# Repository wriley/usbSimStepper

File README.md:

usbSimStepper
=============

This is a half-finished project I started several years ago for a flight simulator panel. It is a USB driver board for 1-2 stepper motors built for instruments from Mike Powell's book Building Simulated Aircraft Instrumentation<sup>1</sup>. Windows programs, such as usbSimCentral<sup>2</sup>, can interface with this board via a DLL<sup>3</sup>.

Relevant blog posts
* http://workbench.freetcp.com/archives/549
* http://workbench.freetcp.com/archives/555
* http://workbench.freetcp.com/archives/571
* http://workbench.freetcp.com/archives/739
* http://workbench.freetcp.com/archives/745

References

1. http://www.mikesflightdeck.com/mfdb/bsai/bsai.html
2. https://github.com/wriley/usbSimCentral
3. https://github.com/wriley/usbSimInstrument

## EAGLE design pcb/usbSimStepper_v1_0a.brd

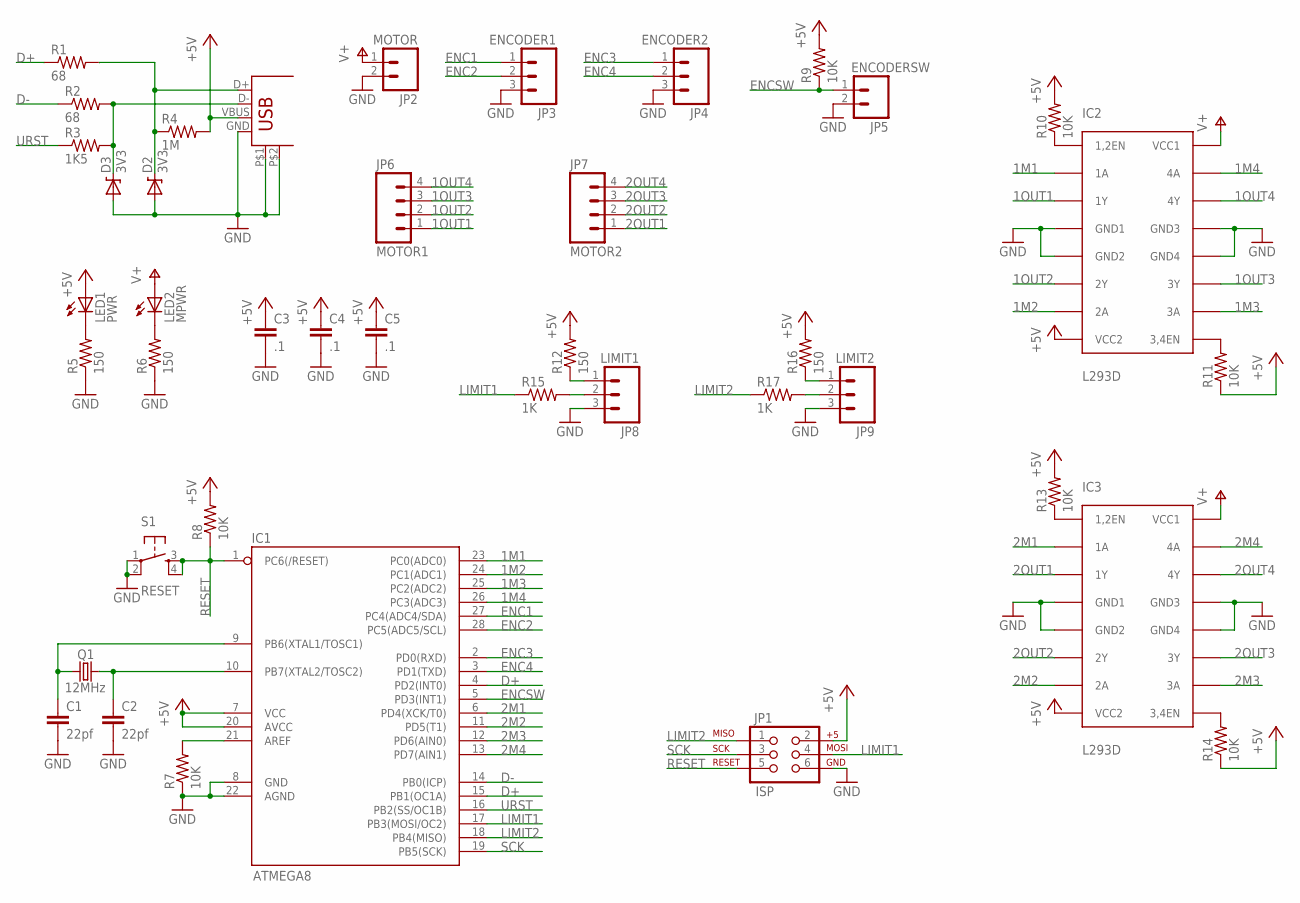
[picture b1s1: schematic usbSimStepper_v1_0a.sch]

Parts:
C1, C2: 22pf; CAP-PTH-SMALL2
C3, C4, C5: .1; CAP-PTH-SMALL2
D2, D3: 3V3; DIODE-ZENER
IC1: ATMEGA8; DIL28-3
IC2, IC3: L293D; DIL16
JP1: ISP; 2X3-NS
JP2: MOTOR; MOLEX-1X2
JP3: ENCODER1; MOLEX-1X3
JP4: ENCODER2; MOLEX-1X3
JP5: ENCODERSW; MOLEX-1X2
JP6: MOTOR1; MOLEX-1X4
JP7: MOTOR2; MOLEX-1X4
JP8: LIMIT1; MOLEX-1X3
JP9: LIMIT2; MOLEX-1X3
LED1: PWR; LED5MM
LED2: MPWR; LED5MM
Q1: 12MHz; HC49US
R1, R2: 68; 0204/7
R3: 1K5; 0204/7
R4: 1M; 0204/7
R5, R6, R12, R16: 150; 0204/7
R7, R8, R9, R10, R11, R13, R14: 10K; 0204/7
R15, R17: 1K; 0204/7
S1: RESET; TACTILE-PTH
X1: USB; USB-B-PTH-VERTICAL

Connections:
1M1: IC1.23 (PC0(ADC0)), IC2.2 (1A)
1M2: IC1.24 (PC1(ADC1)), IC2.7 (2A)
1M3: IC1.25 (PC2(ADC2)), IC2.10 (3A)
1M4: IC1.26 (PC3(ADC3)), IC2.15 (4A)
1OUT1: IC2.3 (1Y), JP6.1
1OUT2: IC2.6 (2Y), JP6.2
1OUT3: IC2.11 (3Y), JP6.3
1OUT4: IC2.14 (4Y), JP6.4
2M1: IC1.6 (PD4(XCK/T0)), IC3.2 (1A)
2M2: IC1.11 (PD5(T1)), IC3.7 (2A)
2M3: IC1.12 (PD6(AIN0)), IC3.10 (3A)
2M4: IC1.13 (PD7(AIN1)), IC3.15 (4A)
2OUT1: IC3.3 (1Y), JP7.1
2OUT2: IC3.6 (2Y), JP7.2
2OUT3: IC3.11 (3Y), JP7.3
2OUT4: IC3.14 (4Y), JP7.4
+5V: C3.1, C4.1, C5.1, IC1.7 (VCC), IC1.20 (AVCC), IC2.8 (VCC2), IC3.8 (VCC2), JP1.2, LED1.A, R4.2, R8.2, R9.2, R10.2, R11.1, R12.2, R13.2, R14.1, R16.2, X1.VBUS
D+: IC1.4 (PD2(INT0)), IC1.15 (PB1(OC1A)), R1.1
D-: IC1.14 (PB0(ICP)), R2.1
ENC1: IC1.27 (PC4(ADC4/SDA)), JP3.1
ENC2: IC1.28 (PC5(ADC5/SCL)), JP3.2
ENC3: IC1.2 (PD0(RXD)), JP4.1
ENC4: IC1.3 (PD1(TXD)), JP4.2
ENCSW: IC1.5 (PD3(INT1)), JP5.1, R9.1
GND: C1.2, C2.2, C3.2, C4.2, C5.2, D2.P$2 (A), D3.P$2 (A), IC1.8 (GND), IC1.22 (AGND), IC2.4 (GND1), IC2.5 (GND2), IC2.12 (GND4), IC2.13 (GND3), IC3.4 (GND1), IC3.5 (GND2), IC3.12 (GND4), IC3.13 (GND3), JP1.6, JP2.2, JP3.3, JP4.3, JP5.2, JP8.3, JP9.3, R5.1, R6.1, R7.1, S1.1, S1.2, X1.GND, X1.P$1, X1.P$2
LIMIT1: IC1.17 (PB3(MOSI/OC2)), JP1.4, R15.1
LIMIT2: IC1.18 (PB4(MISO)), JP1.1, R17.1
unnamed: D3.P$1 (C), R2.2, R3.2, X1.D-
unnamed: D2.P$1 (C), R1.2, R4.1, X1.D+
unnamed: LED1.K (C), R5.2
unnamed: LED2.K (C), R6.2
unnamed: C1.1, IC1.9 (PB6(XTAL1/TOSC1)), Q1.1
unnamed: C2.1, IC1.10 (PB7(XTAL2/TOSC2)), Q1.2
unnamed: IC1.21 (AREF), R7.2
unnamed: JP8.1, R12.1
unnamed: JP8.2, R15.2
unnamed: JP9.1, R16.1
unnamed: IC3.1 (1,2EN), R13.1
unnamed: IC3.9 (3,4EN), R14.2
unnamed: IC2.1 (1,2EN), R10.1
unnamed: IC2.9 (3,4EN), R11.2
unnamed: JP9.2, R17.2
RESET: IC1.1 (PC6(/RESET)), JP1.5, R8.1, S1.3, S1.4
SCK: IC1.19 (PB5(SCK)), JP1.3
URST: IC1.16 (PB2(SS/OC1B)), R3.1
V+: IC2.16 (VCC1), IC3.16 (VCC1), JP2.1, LED2.A

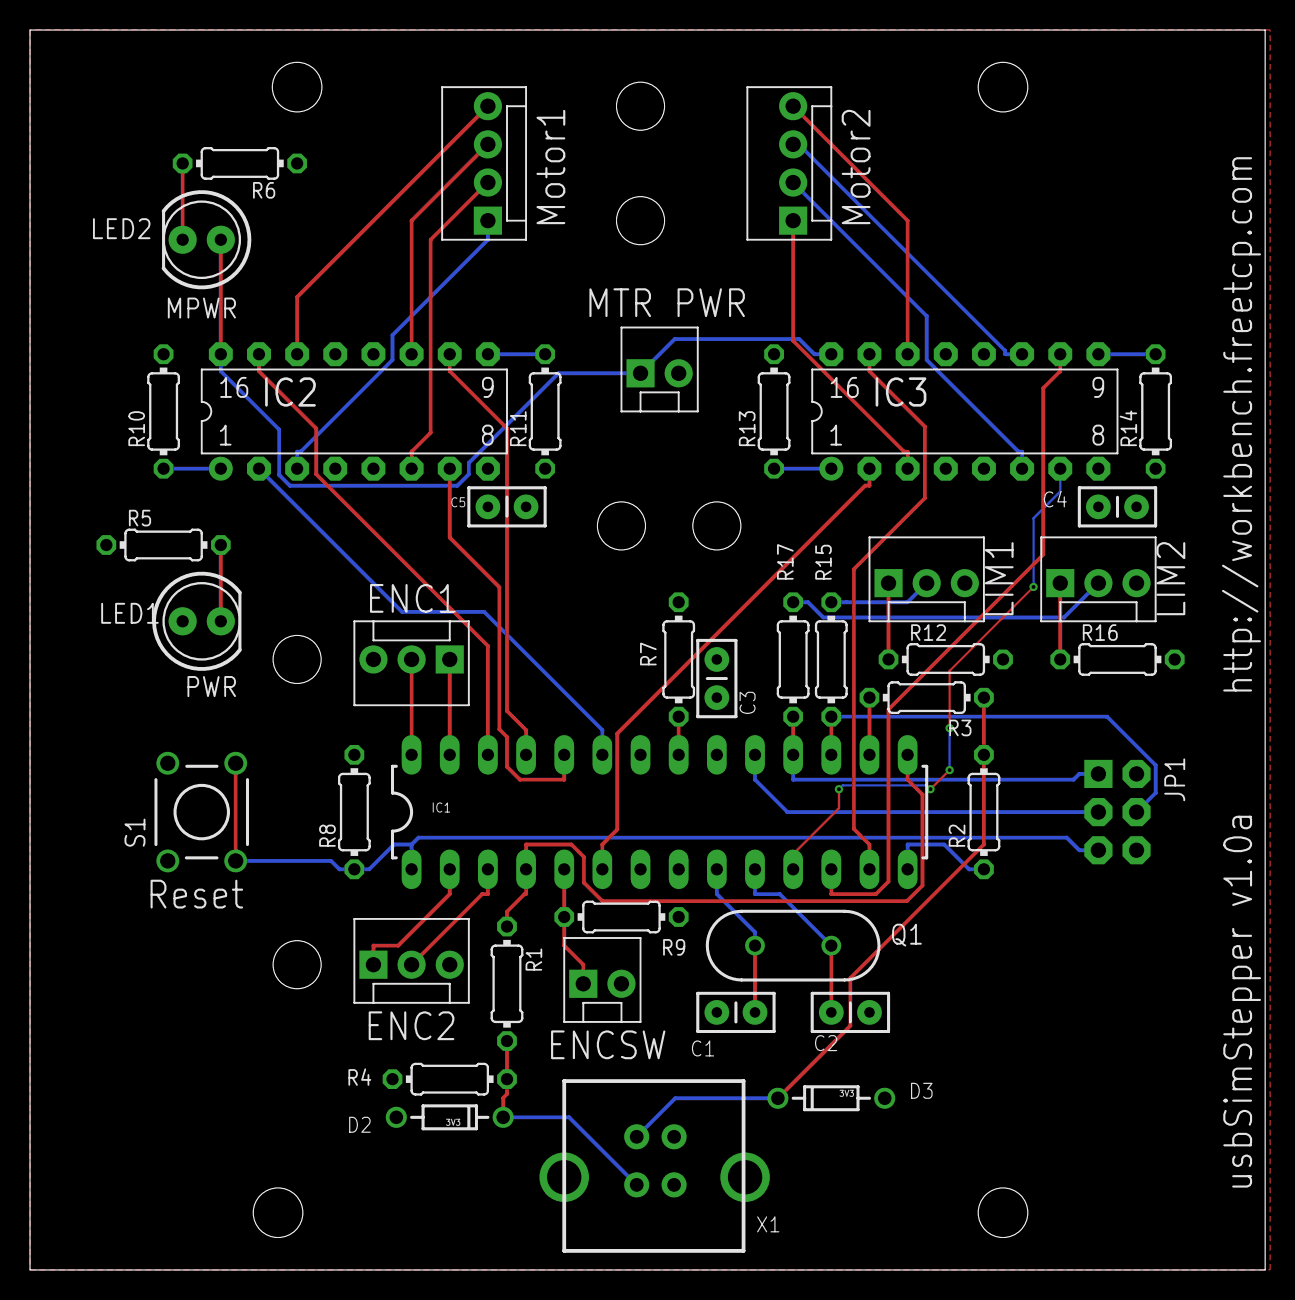
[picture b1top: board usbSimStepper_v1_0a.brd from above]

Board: 2 copper layers, 82.2 x 82.5 mm, 45 parts (0 on the bottom side), 46 nets.

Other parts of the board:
U$1, U$2, U$3, U$4: STAND-OFF

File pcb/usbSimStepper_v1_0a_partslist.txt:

Partlist

Exported from usbSimStepper_v1_0a.brd at 2/13/2012 9:21:40 PM

EAGLE Version 6.1.0 Copyright (c) 1988-2012 CadSoft

Assembly variant: 

Part     Value          Package            Library  Position (inch)       Orientation

C1       22pf           CAP-PTH-SMALL2     SparkFun (1.9 0.675)           R180
C2       22pf           CAP-PTH-SMALL2     SparkFun (2.1 0.675)           R0
C3       .1             CAP-PTH-SMALL2     SparkFun (1.8 1.5)             R90
C4       .1             CAP-PTH-SMALL2     SparkFun (2.8 2)               R0
C5       .1             CAP-PTH-SMALL2     SparkFun (1.2 2)               R0
D2       3V3            DIODE-ZENER        SparkFun (1.1 0.4)             R180
D3       3V3            DIODE-ZENER        SparkFun (2.1 0.45)            R0
IC1      ATMEGA8        DIL28-3            SparkFun (1.65 1.2)            R0
IC2      L293D          DIL16              sgs-thom (0.85 2.25)           R0
IC3      L293D          DIL16              sgs-thom (2.45 2.25)           R0
JP1      ISP            2X3-NS             SparkFun (2.85 1.2)            R270
JP2      MOTOR          MOLEX-1X2          SparkFun (1.6 2.35)            R0
JP3      ENCODER1       MOLEX-1X3          SparkFun (1.1 1.6)             R180
JP4      ENCODER2       MOLEX-1X3          SparkFun (0.9 0.8)             R0
JP5      ENCODERSW      MOLEX-1X2          SparkFun (1.45 0.75)           R0
JP6      MOTOR1         MOLEX-1X4          SparkFun (1.2 2.75)            R90
JP7      MOTOR2         MOLEX-1X4          SparkFun (2 2.75)              R90
JP8      LIMIT1         MOLEX-1X3          SparkFun (2.25 1.8)            R0
JP9      LIMIT2         MOLEX-1X3          SparkFun (2.7 1.8)             R0
LED1     PWR            LED5MM             SparkFun (0.45 1.7)            R0
LED2     MPWR           LED5MM             SparkFun (0.45 2.7)            R180
Q1       12MHz          HC49US             SparkFun (2 0.85)              R0
R1       68             0204/7             resistor (1.25 0.75)           R270
R2       68             0204/7             resistor (2.5 1.2)             R90
R3       1K5            0204/7             resistor (2.35 1.5)            R0
R4       1M             0204/7             resistor (1.1 0.5)             R180
R5       150            0204/7             resistor (0.35 1.9)            R0
R6       150            0204/7             resistor (0.55 2.9)            R180
R7       10K            0204/7             resistor (1.7 1.6)             R270
R8       10K            0204/7             resistor (0.85 1.2)            R90
R9       10K            0204/7             resistor (1.55 0.925)          R0
R10      10K            0204/7             resistor (0.35 2.25)           R90
R11      10K            0204/7             resistor (1.35 2.25)           R90
R12      150            0204/7             resistor (2.4 1.6)             R0
R13      10K            0204/7             resistor (1.95 2.25)           R90
R14      10K            0204/7             resistor (2.95 2.25)           R90
R15      1K             0204/7             resistor (2.1 1.6)             R90
R16      150            0204/7             resistor (2.85 1.6)            R0
R17      1K             0204/7             resistor (2 1.6)               R90
S1       RESET          TACTILE-PTH        SparkFun (0.45 1.2)            R90
X1       USB            USB-B-PTH-VERTICAL SparkFun (1.4 0.05)            R0

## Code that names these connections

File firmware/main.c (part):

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
    wdt_enable(WDTO_1S);
    odDebugInit();
    DDRD = ~(1 << 2);   /* all outputs except PD2 = INT0 */
    PORTD = 0;
    PORTB = 0;          /* no pullups on USB pins */
/* We fake an USB disconnect by pulling D+ and D- to 0 during reset. This is
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    TCCR0 = 5;          /* set prescaler to 1/1024 */
    usbInit();

	DDRB &= ~(_BV(PB3));
	PORTB |= _BV(PB3);
	
	DDRD &= ~(_BV(PD0)|_BV(PD1));
	PORTD |= (_BV(PD0)|_BV(PD1));

	TCNT2 = 0x00; /* Timer 2: Reset counter (periodic timer) */
	TCCR2 = 0x0f; /* Clock / 1024, clear after compare match (CTC) */
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
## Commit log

2009-02-03 Initial import.
2009-02-03 usbSimStepper-v10.sch: added eagle schematic
2009-02-04 finished schematic and created board
2009-02-04 usbSimStepper-v10.brd: checking in unrouted version usbSimStepper-v10-routed.brd: separate file for routed version
2009-02-04 added filter cap for stepper chip
2009-02-05 first attempt at supporting dual stepper motors
2009-02-09 added optical interrupter connections
2009-06-01 added ExpressPCB schematic and PCB files
2009-07-02 change motor power connector
2009-09-23 created directory structure deleted old eagle and ExpressPCB directories
2009-09-23 added l293's
2009-09-24 usbSimStepper.sch: finished schematic usbSimStepper.brd: blank board with standoff holes
2009-09-24 usbSimStepper.brd: first attempt at component placement
2009-09-24 added filter cap for power
2009-09-24 ERC fixes
2009-09-24 some clean up of name/value placement added power and ground planes
2009-09-24 board updates and added limit sensor connections
2009-09-24 v1.0
2009-09-24 renaming for v1.0
2009-09-24 added freerouting.net files added zip of gerber files
2009-09-24 added POV files for Eagle3D
2009-09-24 added firmware: this is untested and is ported from a prototype single stepper breadboard setup
2009-09-24 usbSimStepper_v1_0_schematic.png: added schematic image
2009-09-25 Fixed one typo, compiles now but still untested
2009-09-25 changed USB commands to constants: CMD_SET1, CMD_RESET, etc
2009-12-26 dual motor version tested with single motor
2009-12-27 added lookup table read/write support updated usbSimStepperTest to work with latest trunk firmware
2009-12-28 added raw lookup table
2012-02-09 version 1.0a fixes these board errors 1) No GND on ISP 2) No GND to USB shield 3) usb 1M resistor tied to GND instead of Vcc
2012-02-10 Added driver
2012-02-10 Converted project to VS2010 Express Added Release/usbSimStepperTest.exe
2012-02-11 added notes for repair of PCB v1.0
2012-02-12 updated firmware to AVR Studio 5.0
2012-02-13 work on serial number setting added firmware/usbSimStepper/Release/usbSimStepper.hex
2012-02-14 removed software directory
2012-02-14 pcb: silkscreen updates
